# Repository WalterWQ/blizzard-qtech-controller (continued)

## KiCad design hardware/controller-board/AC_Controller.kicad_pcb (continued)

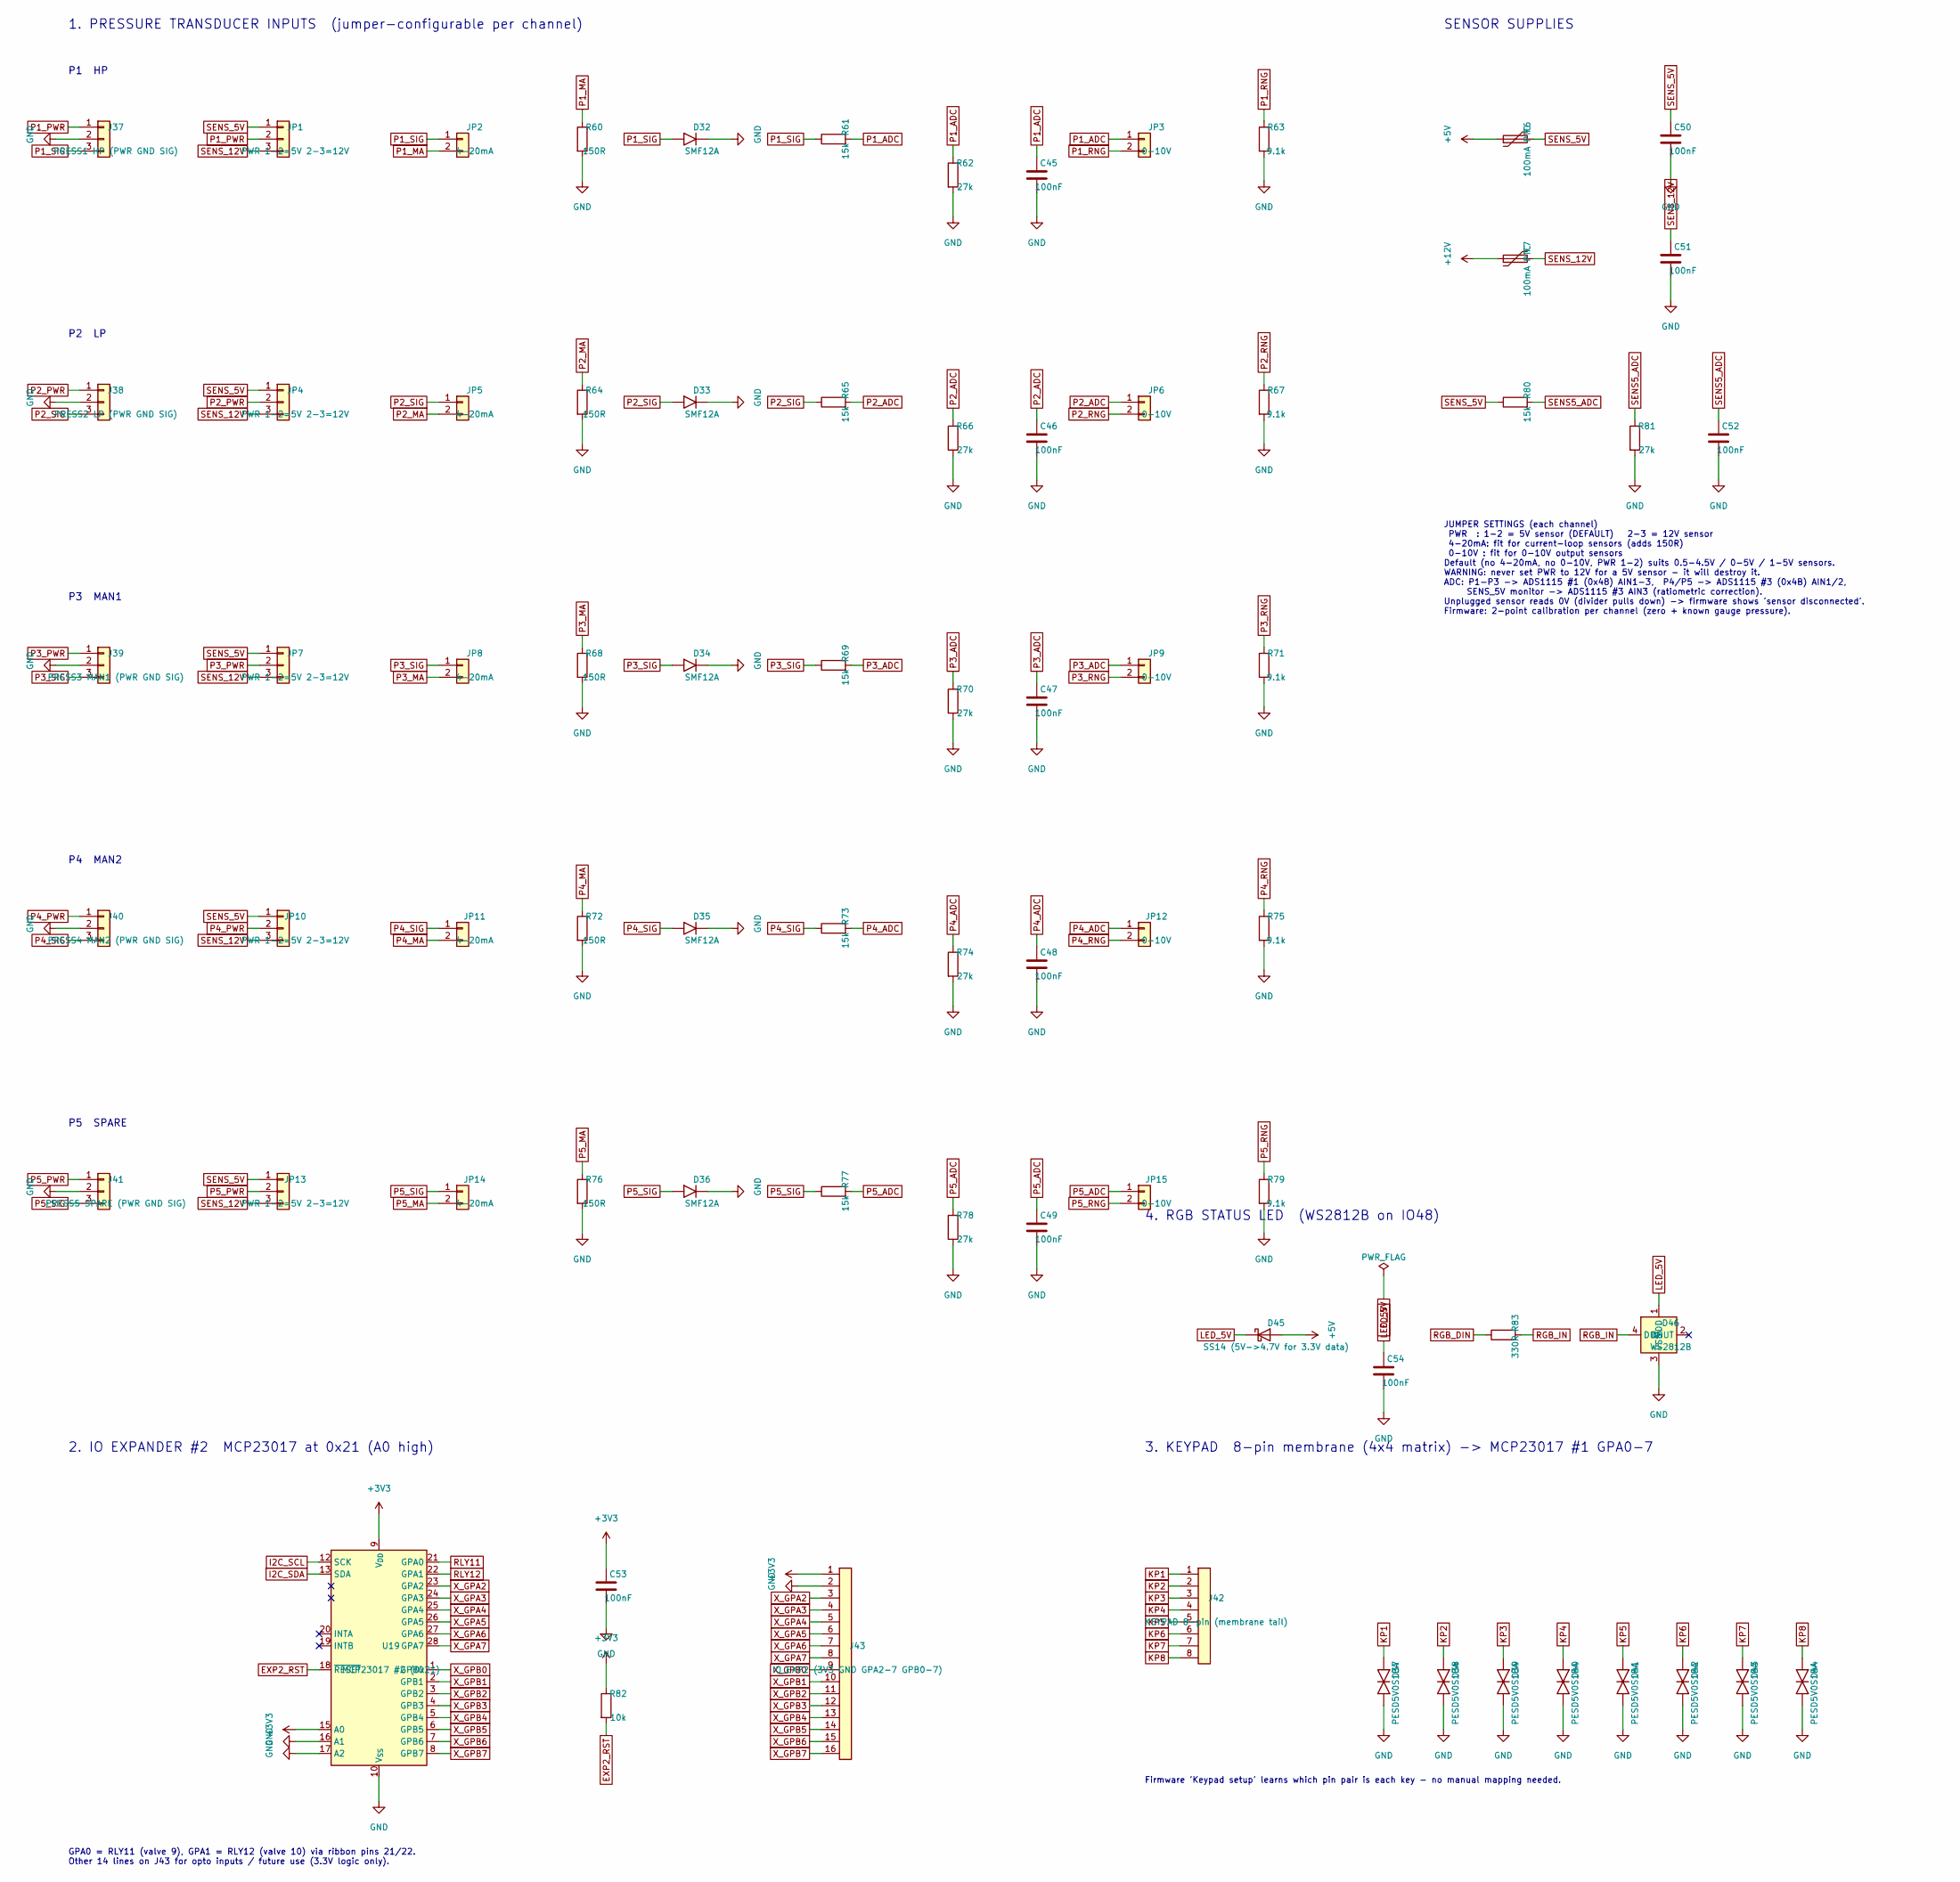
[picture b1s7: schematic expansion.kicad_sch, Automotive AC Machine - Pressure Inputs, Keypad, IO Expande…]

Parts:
C45, C46, C47, C48, C49, C50, C51, C52, C53, C54: 100nF; C_0805_2012Metric
D32, D33, D34, D35, D36: SMF12A; D_SOD-123F
D37, D38, D39, D40, D41, D42, D43, D44: PESD5V0S1BA; D_SOD-323
D45: SS14 (5V->4.7V for 3.3V data); D_SMA
D46: WS2812B; LED_WS2812B_PLCC4_5.0x5.0mm_P3.2mm
F6, F7: 100mA PTC; Fuse_1206_3216Metric
J37: PRESS1 HP (PWR GND SIG); TerminalBlock_Phoenix_MKDS-1,5-3-5.08_1x03_P5.08mm_Horizont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
J38: PRESS2 LP (PWR GND SIG); TerminalBlock_Phoenix_MKDS-1,5-3-5.08_1x03_P5.08mm_Horizont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
J39: PRESS3 MAN1 (PWR GND SIG); TerminalBlock_Phoenix_MKDS-1,5-3-5.08_1x03_P5.08mm_Horizont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
J40: PRESS4 MAN2 (PWR GND SIG); TerminalBlock_Phoenix_MKDS-1,5-3-5.08_1x03_P5.08mm_Horizont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
J41: PRESS5 SPARE (PWR GND SIG); TerminalBlock_Phoenix_MKDS-1,5-3-5.08_1x03_P5.08mm_Horizont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
J42: KEYPAD 8-pin (membrane tail); PinHeader_1x08_P2.54mm_Vertical
J43: IO_EXP2 (3V3 GND GPA2-7 GPB0-7); PinHeader_1x16_P2.54mm_Vertical
JP1, JP4, JP7, JP10, JP13: PWR 1-2=5V 2-3=12V; PinHeader_1x03_P2.54mm_Vertical
JP2, JP5, JP8, JP11, JP14: 4-20mA; PinHeader_1x02_P2.54mm_Vertical
JP3, JP6, JP9, JP12, JP15: 0-10V; PinHeader_1x02_P2.54mm_Vertical
R60, R64, R68, R72, R76: 150R; R_0805_2012Metric
R61, R65, R69, R73, R77, R80: 15k; R_0805_2012Metric
R62, R66, R70, R74, R78, R81: 27k; R_0805_2012Metric
R63, R67, R71, R75, R79: 9.1k; R_0805_2012Metric
R82: 10k; R_0805_2012Metric
R83: 330R; R_0805_2012Metric
U19: MCP23017 #2 (0x21); SOIC-28W_7.5x17.9mm_P1.27mm

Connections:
+3V3: C53.1, J43.1, R82.1, U19.9 (V_{DD}), U19.15 (A0); also elsewhere on the board
+5V: D45.2 (A), F6.1; also elsewhere on the board
+12V: F7.1; also elsewhere on the board
EXP2_RST: R82.2, U19.18 (~RESET)
GND: C45.2, C46.2, C47.2, C48.2, C49.2, C50.2, C51.2, C52.2, C53.2, C54.2, D32.2 (A), D33.2 (A), D34.2 (A), D35.2 (A), D36.2 (A), D37.2 (A2), D38.2 (A2), D39.2 (A2), D40.2 (A2), D41.2 (A2), D42.2 (A2), D43.2 (A2), D44.2 (A2), D46.3 (VSS), J37.2, J38.2, J39.2, J40.2, J41.2, J43.2, R60.2, R62.2, R63.2, R64.2, R66.2, R67.2, R68.2, R70.2, R71.2, R72.2, R74.2, R75.2, R76.2, R78.2, R79.2, R81.2, U19.10 (V_{SS}), U19.16 (A1), U19.17 (A2); also elsewhere on the board
I2C_SCL: U19.12 (SCK); also elsewhere on the board
I2C_SDA: U19.13 (SDA); also elsewhere on the board
KP1: D37.1 (A1), J42.1; also elsewhere on the board
KP2: D38.1 (A1), J42.2; also elsewhere on the board
KP3: D39.1 (A1), J42.3; also elsewhere on the board
KP4: D40.1 (A1), J42.4; also elsewhere on the board
KP5: D41.1 (A1), J42.5; also elsewhere on the board
KP6: D42.1 (A1), J42.6; also elsewhere on the board
KP7: D43.1 (A1), J42.7; also elsewhere on the board
KP8: D44.1 (A1), J42.8; also elsewhere on the board
LED_5V: C54.1, D45.1 (K), D46.1 (VDD)
P1_ADC: C45.1, JP3.1, R61.2, R62.1; also elsewhere on the board
P1_MA: JP2.2, R60.1
P1_PWR: J37.1, JP1.2
P1_RNG: JP3.2, R63.1
P1_SIG: D32.1 (K), J37.3, JP2.1, R61.1
P2_ADC: C46.1, JP6.1, R65.2, R66.1; also elsewhere on the board
P2_MA: JP5.2, R64.1
P2_PWR: J38.1, JP4.2
P2_RNG: JP6.2, R67.1
P2_SIG: D33.1 (K), J38.3, JP5.1, R65.1
P3_ADC: C47.1, JP9.1, R69.2, R70.1; also elsewhere on the board
P3_MA: JP8.2, R68.1
P3_PWR: J39.1, JP7.2
P3_RNG: JP9.2, R71.1
P3_SIG: D34.1 (K), J39.3, JP8.1, R69.1
P4_ADC: C48.1, JP12.1, R73.2, R74.1; also elsewhere on the board
P4_MA: JP11.2, R72.1
P4_PWR: J40.1, JP10.2
P4_RNG: JP12.2, R75.1
P4_SIG: D35.1 (K), J40.3, JP11.1, R73.1
P5_ADC: C49.1, JP15.1, R77.2, R78.1; also elsewhere on the board
P5_MA: JP14.2, R76.1
P5_PWR: J41.1, JP13.2
P5_RNG: JP15.2, R79.1
P5_SIG: D36.1 (K), J41.3, JP14.1, R77.1
RGB_DIN: R83.1; also elsewhere on the board
RGB_IN: D46.4 (DIN), R83.2
RLY11: U19.21 (GPA0); also elsewhere on the board
RLY12: U19.22 (GPA1); also elsewhere on the board
SENS5_ADC: C52.1, R80.2, R81.1; also elsewhere on the board
SENS_5V: C50.1, F6.2, JP1.1, JP4.1, JP7.1, JP10.1, JP13.1, R80.1
SENS_12V: C51.1, F7.2, JP1.3, JP4.3, JP7.3, JP10.3, JP13.3
X_GPA2: J43.3, U19.23 (GPA2)
X_GPA3: J43.4, U19.24 (GPA3)
X_GPA4: J43.5, U19.25 (GPA4)
X_GPA5: J43.6, U19.26 (GPA5)
X_GPA6: J43.7, U19.27 (GPA6)
X_GPA7: J43.8, U19.28 (GPA7)
X_GPB0: J43.9, U19.1 (GPB0)
X_GPB1: J43.10, U19.2 (GPB1)
X_GPB2: J43.11, U19.3 (GPB2)
X_GPB3: J43.12, U19.4 (GPB3)
X_GPB4: J43.13, U19.5 (GPB4)
X_GPB5: J43.14, U19.6 (GPB5)
X_GPB6: J43.15, U19.7 (GPB6)
X_GPB7: J43.16, U19.8 (GPB7)

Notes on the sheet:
1. PRESSURE TRANSDUCER INPUTS (jumper-configurable per channel)
P1 HP
P2 LP
P3 MAN1
P4 MAN2
P5 SPARE
SENSOR SUPPLIES
JUMPER SETTINGS (each channel) PWR : 1-2 = 5V sensor (DEFAULT) 2-3 = 12V sensor 4-20mA: fit for current-loop sensors (adds 150R) 0-10V : fit for 0-10V output sensors Default (no 4-20mA, no 0-10V, PWR 1-2) suits 0.5-4.5V / 0-5V / 1-5V sensors. WARNING: never set PWR to 12V for a 5V sensor - it will 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
2. IO EXPANDER #2 MCP23017 at 0x21 (A0 high)
GPA0 = RLY11 (valve 9), GPA1 = RLY12 (valve 10) via ribbon pins 21/22. Other 14 lines on J43 for opto inputs / future use (3.3V logic only).
3. KEYPAD 8-pin membrane (4x4 matrix) -> MCP23017 #1 GPA0-7
Firmware 'Keypad setup' learns which pin pair is each key - no manual mapping needed.
4. RGB STATUS LED (WS2812B on IO48)

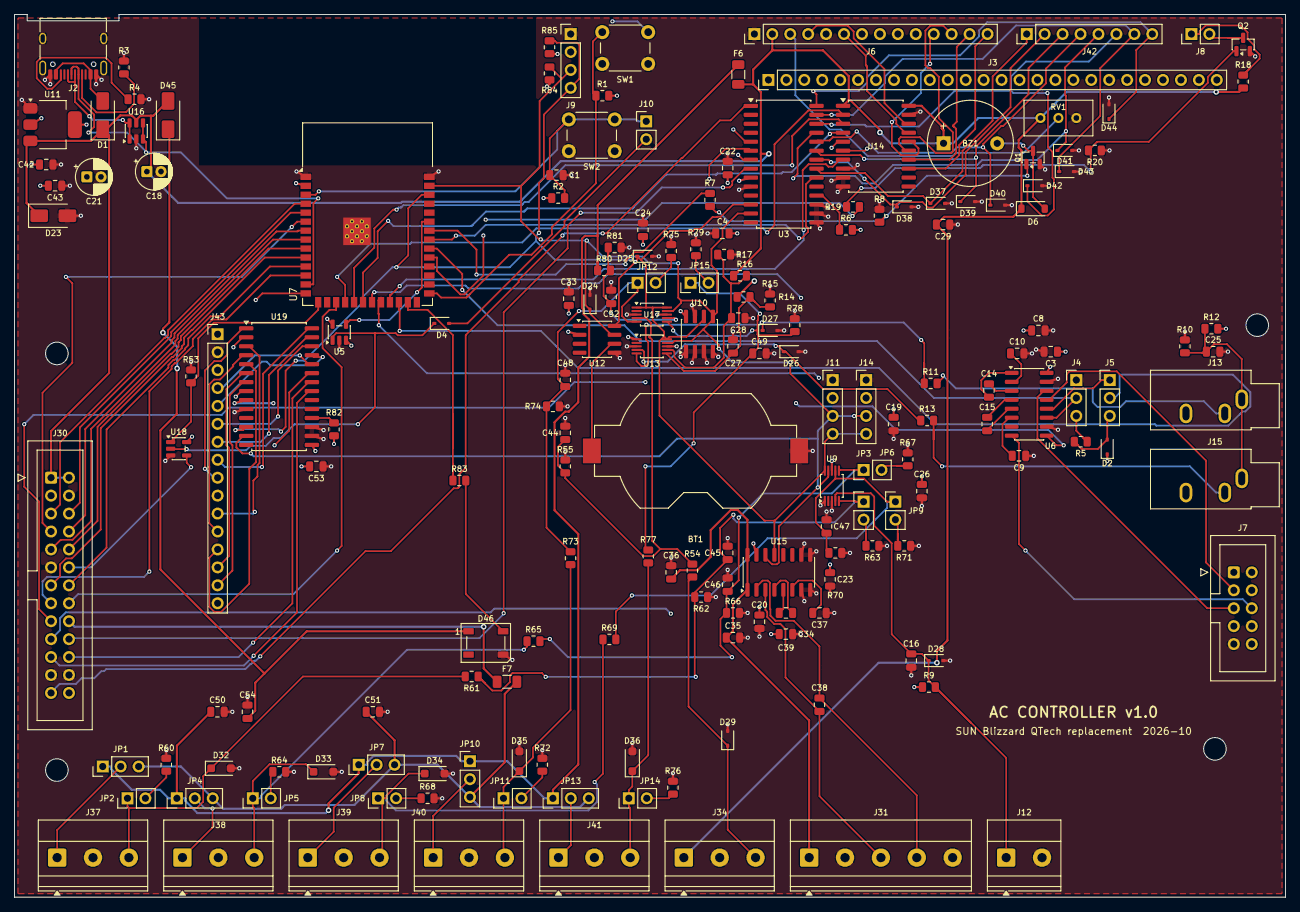
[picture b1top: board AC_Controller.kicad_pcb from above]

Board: 4 copper layers, 180.0 x 125.0 mm, 183 parts (0 on the bottom side), 142 nets.

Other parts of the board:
H1, H2, H3, H4: MountingHole_3.2mm_M3

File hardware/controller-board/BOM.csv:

Line,Qty per board,Part to buy,Package,What it is,References,Notes
1,2,MCP23017-E/SO,SOIC-28 wide,16-bit I/O expander,"U3, U19",
2,1,TPS3823-33DBVR,SOT-23-5,Watchdog / reset chip,U5,
3,1,MAX3232ESE+,SOIC-16,RS-232 transceiver,U6,
4,1,ESP32-S3-WROOM-1-N8 (or -N16R8),Module,Microcontroller module with Wi-Fi,U7,
5,3,ADS1115IDGSR,MSOP-10 (VSSOP),16-bit 4-channel ADC,"U9, U13, U17",
6,1,MB85RC256VPNF,SOIC-8,256kbit FRAM memory,U10,
7,1,AMS1117-3.3,SOT-223,3.3V regulator,U11,
8,1,DS3231MZ+,SOIC-8,Real-time clock,U12,
9,1,SN74HCT245DWR,SOIC-20 wide,8-bit level shifter for LCD,U14,
10,1,NAU7802KGI,SOIC-16,Load-cell ADC,U15,
11,1,USBLC6-2SC6,SOT-23-6,USB ESD protection,U16,
12,1,SN74LVC1G08DBVR,SOT-23-5,Single AND gate,U18,
13,2,AO3400A,SOT-23,N-channel MOSFET,"Q1, Q2",
14,2,SS14,SMA,1A Schottky diode,"D1, D45",
15,2,BAT54WS,SOD-323,Small Schottky diode,"D2, D4",
16,1,1N4148W,SOD-123,Small signal diode,D6,
17,1,SMAJ6.0A,SMA,"TVS diode, 5V rail",D23,
18,14,PESD5V0S1BA,SOD-323,ESD protection diode,"D24, D25, D26, D27, D28, D29, D37, D38, D39, D40, D41, D42, D43, D44",
19,5,SMF12A,SOD-123F,"TVS diode, sensor input","D32, D33, D34, D35, D36",
20,1,WS2812B,5050,RGB status LED,D46,
21,10,10k 1% 0805,0805,Resistor,"R1, R2, R6, R9, R10, R12, R15, R16, R17, R82",
22,2,5.1k 1% 0805,0805,Resistor,"R3, R4",
23,3,1k 1% 0805,0805,Resistor,"R5, R11, R13",
24,2,100R 1% 0805,0805,Resistor,"R7, R19",
25,3,100k 1% 0805,0805,Resistor,"R8, R20, R53",
26,1,47k 1% 0805,0805,Resistor,R14,
27,1,10R 1% 0805,0805,Resistor,R18,
28,7,15k 1% 0805,0805,Resistor,"R54, R61, R65, R69, R73, R77, R80",
29,7,27k 1% 0805,0805,Resistor,"R55, R62, R66, R70, R74, R78, R81",
30,5,150R 1% 0805,0805,Resistor,"R60, R64, R68, R72, R76",
31,5,9.1k 1% 0805,0805,Resistor,"R63, R67, R71, R75, R79",
32,1,330R 1% 0805,0805,Resistor,R83,
33,2,4.7k 1% 0805,0805,Resistor,"R84, R85",
34,1,Bourns 3296W-1-103LF,3296W trimmer,10k trimmer (LCD contrast),RV1,
35,1,1uF 16V X7R 0805,0805,Capacitor,C1,
36,33,100nF X7R 0805,0805,Capacitor,"C3, C4, C8, C9, C10, C14, C15, C16, C19, C20, C22, C23, C26, C27, C28, C29, C33, C36, C37, C38, C42, C43, C44, C45, C46, C47, C48, C49, C50, C51, C52, C53, C54",
37,1,10uF 16V electrolytic,"Radial 5mm, 2mm pitch",Capacitor,C18,
38,1,22uF 16V electrolytic,"Radial 5mm, 2mm pitch",Capacitor,C21,
39,4,10uF 16V X5R 0805,0805,Capacitor,"C24, C25, C34, C35",
40,1,330pF X7R 0805,0805,Capacitor,C39,
41,2,Littelfuse 1206L010 (100mA hold),1206,Resettable fuse,"F6, F7",
42,1,HRO TYPE-C-31-M-12,USB-C,USB-C socket,J2,
43,1,"1x26 pin header, 2.54mm",2.54mm pin header,Pin header,J3,Labels: Front IO; Not connected to anything - decide whether to keep
44,7,"1x3 pin header, 2.54mm",2.54mm pin header,Pin header,"J4, J5, JP1, JP4, JP7, JP10, JP13","Labels: PRINTER_TTL, PRN_SEL, PWR 1-2=5V 2-3=12V; Fit a jumper shunt"
45,1,"1x14 pin header, 2.54mm",2.54mm pin header,Pin header,J6,Labels: LCD
46,1,"2x5 (10-way) box header, 2.54mm",2.54mm box header,Ribbon header,J7,Labels: PRINTER_RS232
47,12,"1x2 pin header, 2.54mm",2.54mm pin header,Pin header,"J8, J10, JP2, JP3, JP5, JP6, JP8, JP9, JP11, JP12, JP14, JP15","Labels: 0-10V, 4-20mA, LCD_BL, WDT_EN; Shunt only if the sensor needs it"
48,3,"1x4 pin header, 2.54mm",2.54mm pin header,Pin header,"J9, J11, J14","Labels: AMBIENT, Conn_01x04, I2C_EXP"
49,1,"Phoenix MKDS 1,5/2-5,08 (1715721) or any 5.08mm 2-way",5.08mm screw terminal,Screw terminal,J12,Labels: TANK_TEMP
50,2,CUI SJ1-3533NG,3.5mm jack,3.5mm jack for current clamp,"J13, J15","Labels: CT_COMP, CT_PUMP"
51,1,"2x13 (26-way) box header, 2.54mm",2.54mm box header,Ribbon header,J30,Labels: Interconnect 2x13 IDC
52,1,"Phoenix MKDS 1,5/5-5,08 (1715750) or any 5.08mm 5-way",5.08mm screw terminal,Screw terminal,J31,Labels: LOAD_CELL (E+ E- S+ S- SHLD)
53,6,"Phoenix MKDS 1,5/3-5,08 (1715734) or any 5.08mm 3-way",5.08mm screw terminal,Screw terminal,"J34, J37, J38, J39, J40, J41","Labels: LEAK_SENSOR (+5V GND SIG), PRESS1 HP (PWR GND SIG), PRESS2 LP (PWR GND SIG), PRESS3 MAN1 (PWR GND SIG), PRESS4 MAN2 (PWR GND SIG), PRESS5 SPARE (PWR GND SIG)"
54,1,"1x8 pin header, 2.54mm",2.54mm pin header,Pin header,J42,Labels: KEYPAD 8-pin (membrane tail)
55,1,"1x16 pin header, 2.54mm",2.54mm pin header,Pin header,J43,Labels: IO_EXP2 (3V3 GND GPA2-7 GPB0-7)
56,2,6x6mm tactile switch,6mm tactile,Push button,"SW1, SW2",
57,1,"5V magnetic buzzer, 12mm","12mm buzzer, 7.6mm pitch",Buzzer,BZ1,
58,1,Keystone 1058,CR2032 holder,CR2032 holder,BT1,
Total,,Total parts placed per board / parts to buy,,,,

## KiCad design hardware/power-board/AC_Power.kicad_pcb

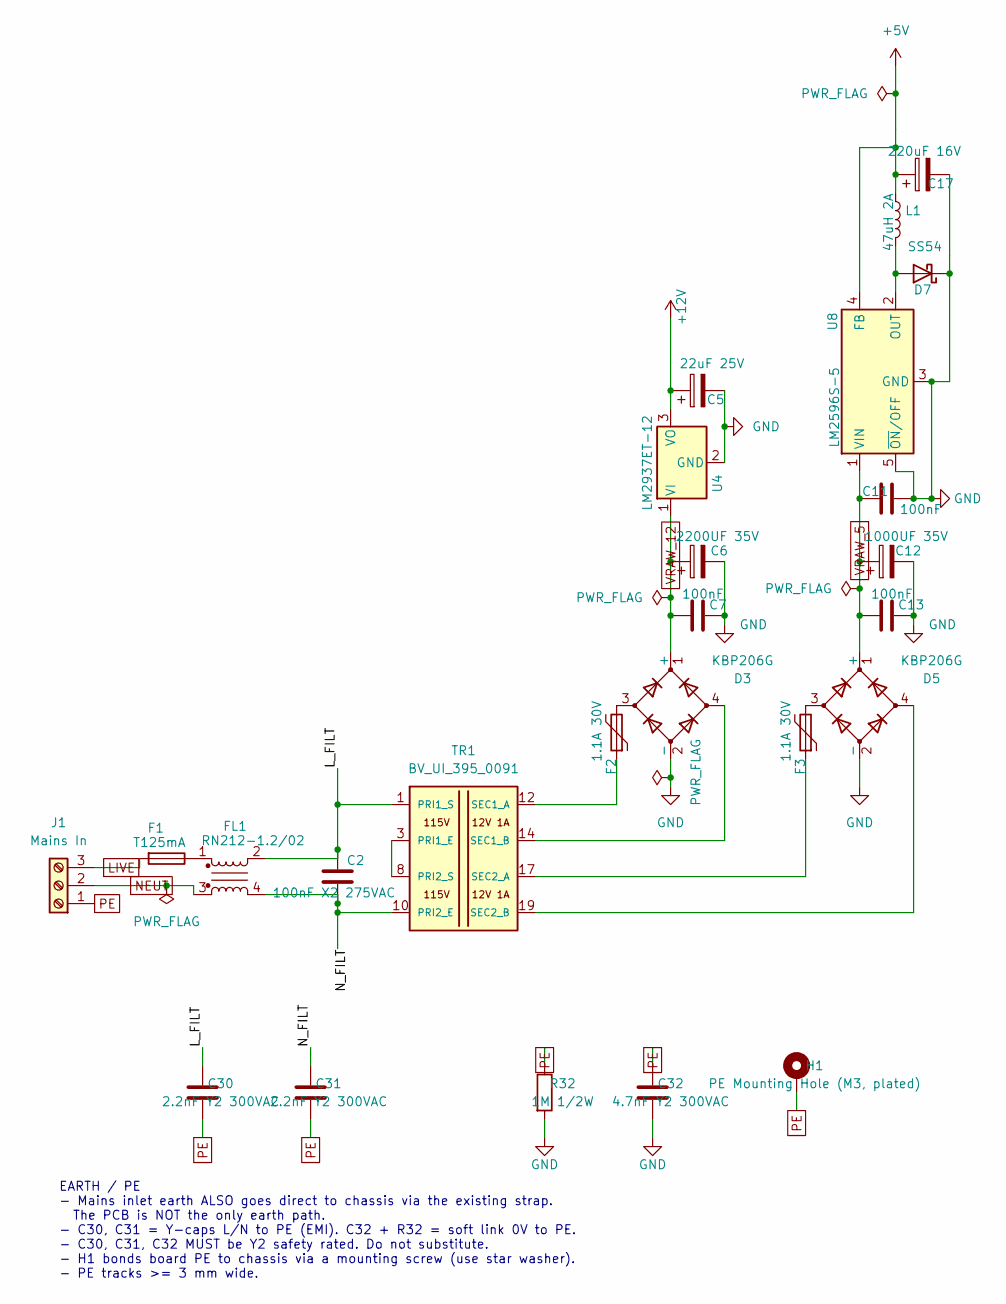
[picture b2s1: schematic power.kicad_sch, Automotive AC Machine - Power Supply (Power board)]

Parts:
C2: 100nF X2 275VAC; C_Rect_L13.0mm_W6.0mm_P10.00mm_FKS3_FKP3_MKS4
C5: 22uF 25V; CP_Radial_D5.0mm_P2.00mm
C6: 2200UF 35V; CP_Radial_D16.0mm_P7.50mm
C7, C11, C13: 100nF; C_0805_2012Metric
C12: 1000UF 35V; CP_Radial_D12.5mm_P5.00mm
C17: 220uF 16V; CP_Radial_D8.0mm_P3.50mm
C30, C31: 2.2nF Y2 300VAC; C_Disc_D7.5mm_W5.0mm_P10.00mm
C32: 4.7nF Y2 300VAC; C_Disc_D7.5mm_W5.0mm_P10.00mm
D3, D5: KBP206G; KBP_P-AC-AC-M
D7: SS54; D_SMC
F1: T125mA; Fuseholder_Cylinder-5x20mm_Schurter_FAB_0031-355x_Horizonta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
F2, F3: 1.1A 30V; Fuse_1812_4532Metric
FL1: RN212-1.2/02; Choke_Schaffner_RN212-04-12.5x18.0mm
H1: PE Mounting Hole (M3, plated); MountingHole_3.2mm_M3_Pad_Via
J1: Mains In; KF7.62_3P
L1: 47uH 2A; L_12x12mm_H8mm
R32: 1M 1/2W; R_Axial_DIN0414_L11.9mm_D4.5mm_P15.24mm_Horizontal
TR1: BV_UI_395_0091; Hahn_UI39_BV_UI_395
U4: LM2937ET-12; TO-220-3_Vertical
U8: LM2596S-5; TO-263-5_TabPin3

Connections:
+5V: C17.1, L1.1, U8.4 (FB); also elsewhere on the board
+12V: C5.1, U4.3 (VO); also elsewhere on the board
GND: C5.2, C6.2, C7.1, C11.1, C12.2, C13.1, C17.2, C32.2, D3.2 (-), D5.2 (-), D7.1 (K), R32.2, U4.2 (GND), U8.3 (GND), U8.5 (~ON/OFF); also elsewhere on the board
LIVE: F1.2, J1.3; also elsewhere on the board
L_FILT: C2.2, C30.1, FL1.2, TR1.1 (PRI1_S)
NEUT: FL1.3, J1.2; also elsewhere on the board
N_D3.3: D3.3, F2.2
N_D3.4: D3.4, TR1.14 (SEC1_B)
N_D5.3: D5.3, F3.2
N_D5.4: D5.4, TR1.19 (SEC2_B)
N_D7.2: D7.2 (A), L1.2, U8.2 (OUT)
N_F1.1: F1.1, FL1.1
N_F2.1: F2.1, TR1.12 (SEC1_A)
N_F3.1: F3.1, TR1.17 (SEC2_A)
N_FILT: C2.1, C31.1, FL1.4, TR1.10 (PRI2_E)
N_TR1.3: TR1.3 (PRI1_E), TR1.8 (PRI2_S)
PE: C30.2, C31.2, C32.1, H1.1, J1.1, R32.1; also elsewhere on the board
VRAW_5: C11.2, C12.1, C13.2, D5.1 (+), U8.1 (VIN)
VRAW_12: C6.1, C7.2, D3.1 (+), U4.1 (VI)

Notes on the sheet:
EARTH / PE - Mains inlet earth ALSO goes direct to chassis via the existing strap. The PCB is NOT the only earth path. - C30, C31 = Y-caps L/N to PE (EMI). C32 + R32 = soft link 0V to PE. - C30, C31, C32 MUST be Y2 safety rated. Do not substitute. - H1 bonds board PE to chassis via a mounting screw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

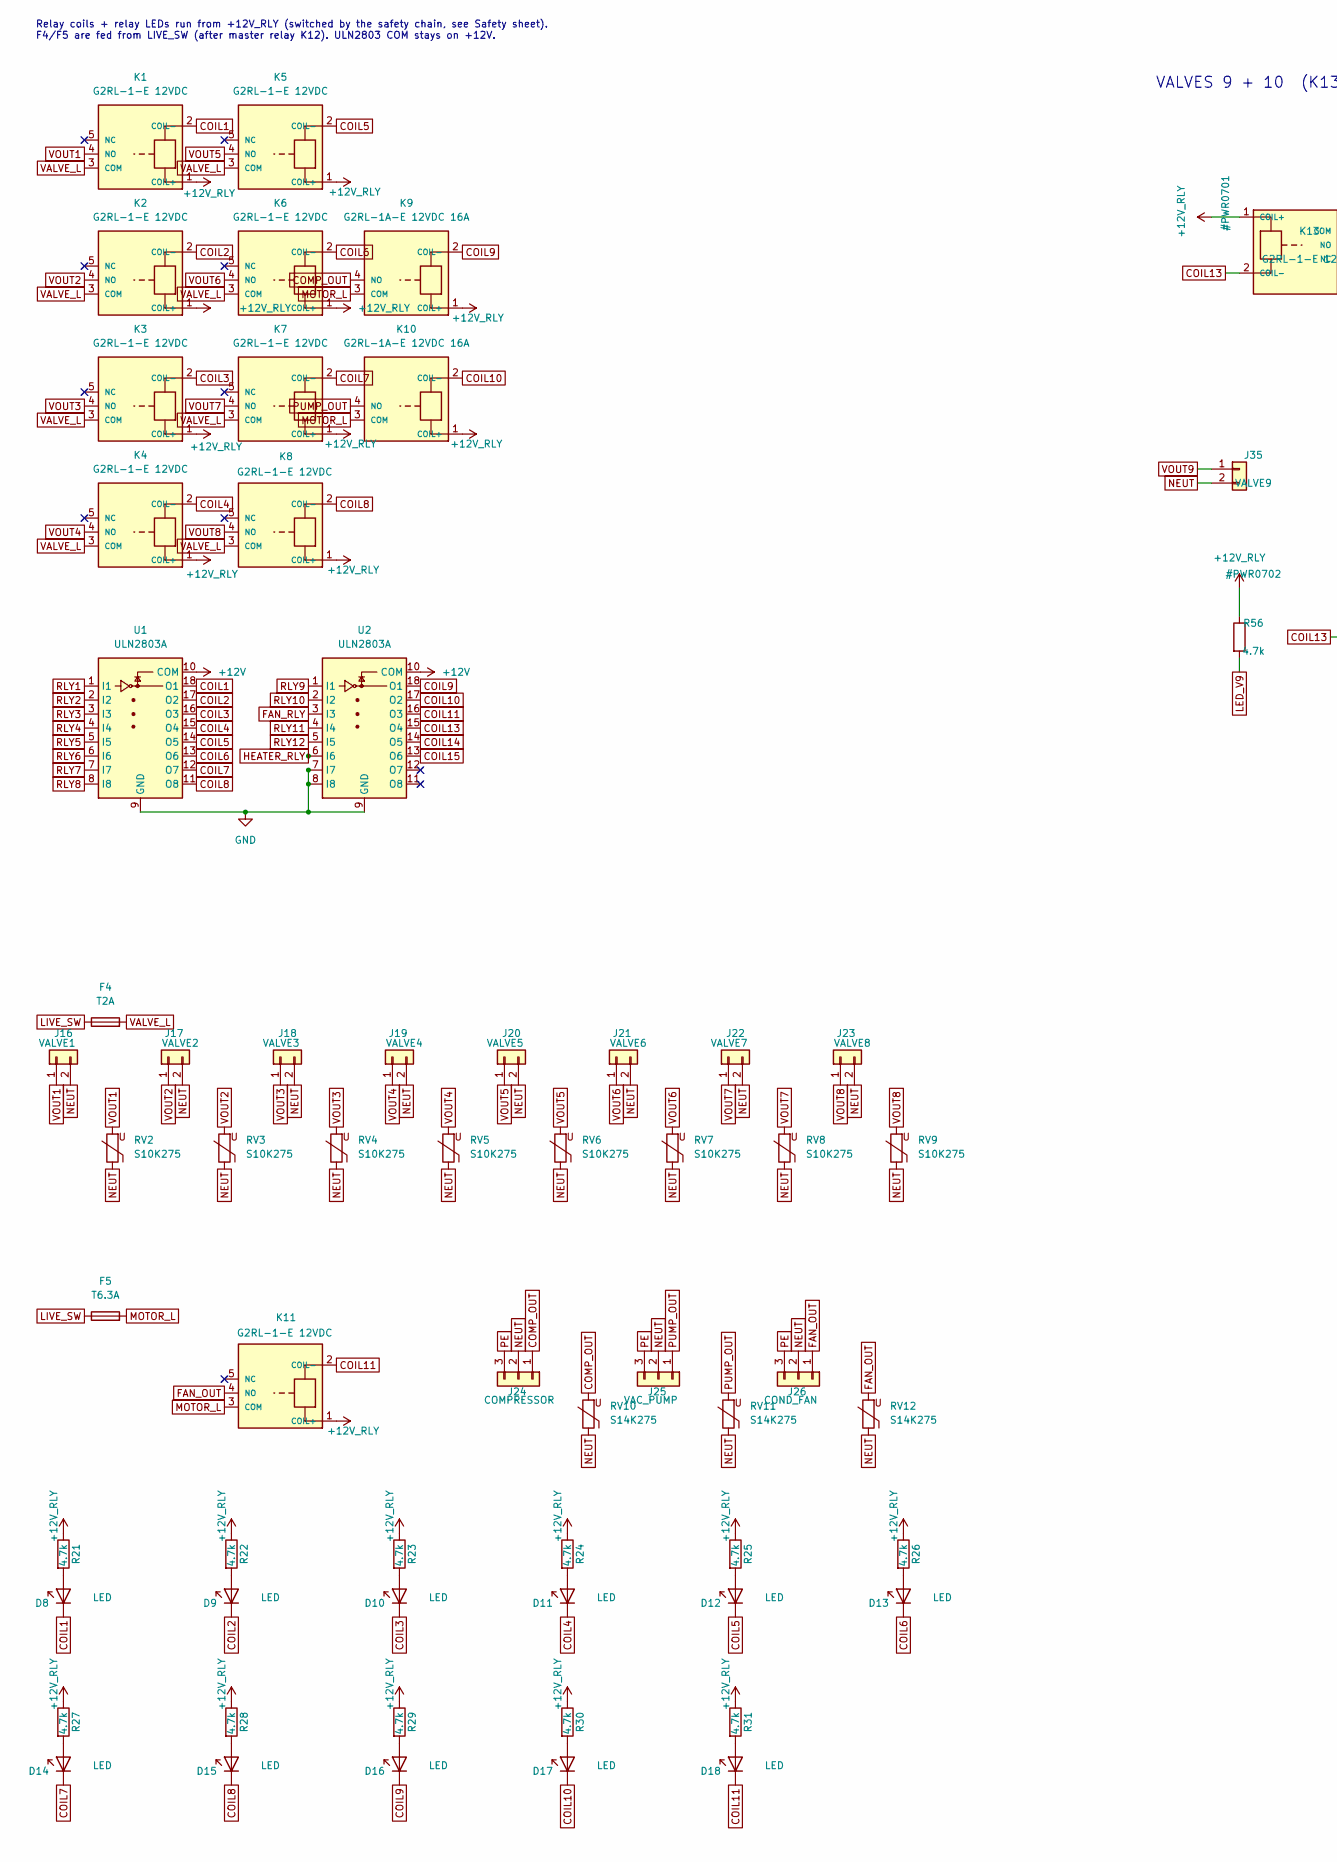
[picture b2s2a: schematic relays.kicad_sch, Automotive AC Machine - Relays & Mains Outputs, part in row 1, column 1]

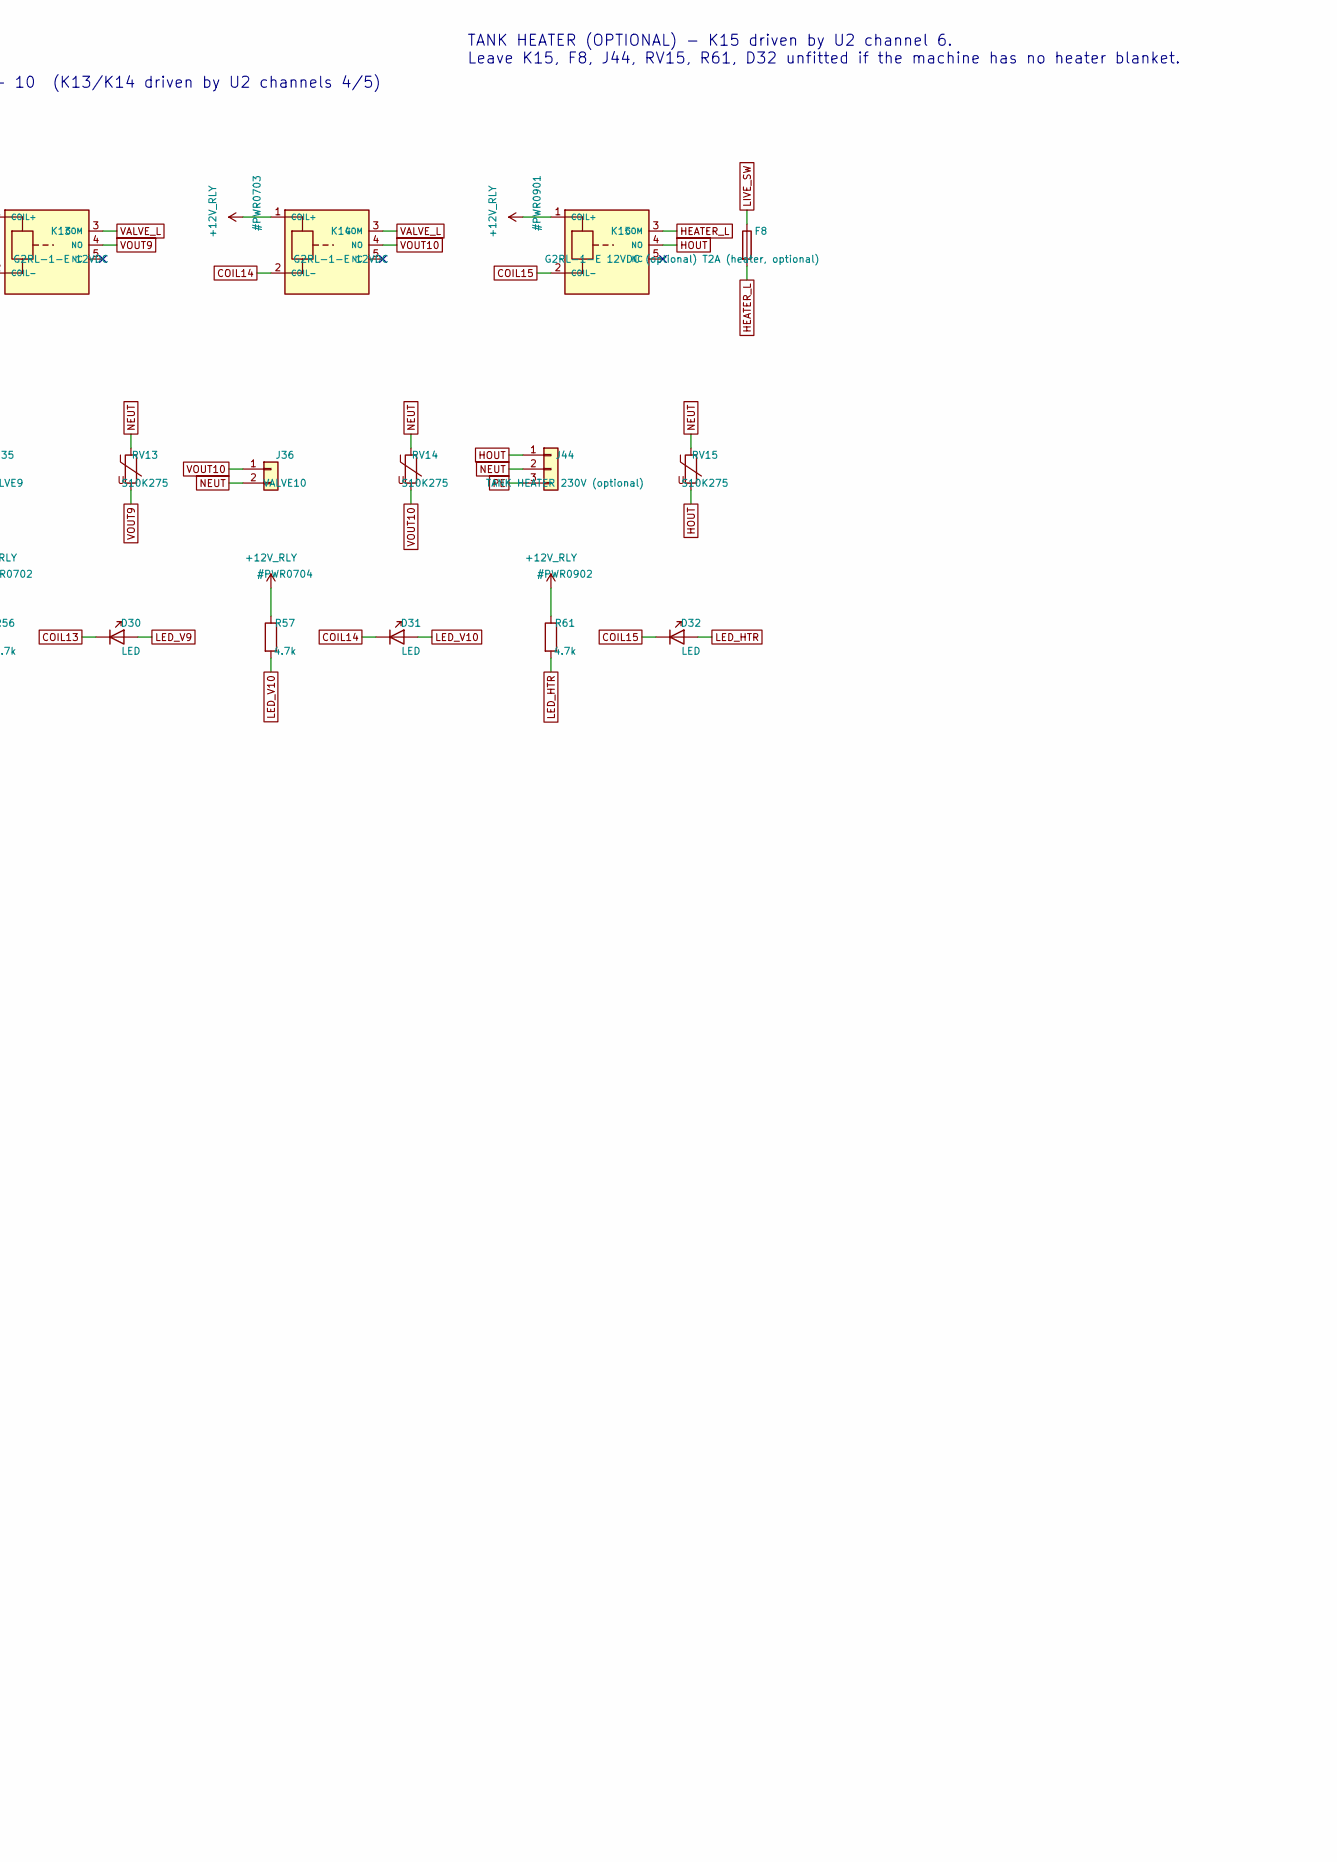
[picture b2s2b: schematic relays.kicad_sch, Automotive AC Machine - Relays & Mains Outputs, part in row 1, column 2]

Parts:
D8, D9, D10, D11, D12, D13, D14, D15, D16, D17, D18, D30, D31, D32: LED; LED_0805_2012Metric
F4: T2A; Fuseholder_Cylinder-5x20mm_Schurter_FAB_0031-355x_Horizonta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
F5: T6.3A; Fuseholder_Cylinder-5x20mm_Schurter_FAB_0031-355x_Horizonta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
F8: T2A (heater, optional); Fuseholder_Cylinder-5x20mm_Schurter_FAB_0031-355x_Horizonta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
J16: VALVE1; KF7.62_2P
J17: VALVE2; KF7.62_2P
J18: VALVE3; KF7.62_2P
J19: VALVE4; KF7.62_2P
J20: VALVE5; KF7.62_2P
J21: VALVE6; KF7.62_2P
J22: VALVE7; KF7.62_2P
J23: VALVE8; KF7.62_2P
J24: COMPRESSOR; KF7.62_3P
J25: VAC_PUMP; KF7.62_3P
J26: COND_FAN; KF7.62_3P
J35: VALVE9; KF7.62_2P
J36: VALVE10; KF7.62_2P
J44: TANK HEATER 230V (optional); KF7.62_3P
K1, K2, K3, K4, K5, K6, K7, K8, K11, K13, K14: G2RL-1-E 12VDC; Relay_G2RL-1-E_QT
K9, K10: G2RL-1A-E 12VDC 16A; Relay_G2RL-1A-E_QT
K15: G2RL-1-E 12VDC (optional); Relay_G2RL-1-E_QT
R21, R22, R23, R24, R25, R26, R27, R28, R29, R30, R31, R56, R57, R61: 4.7k; R_0805_2012Metric
RV2, RV3, RV4, RV5, RV6, RV7, RV8, RV9, RV13, RV14, RV15: S10K275; RV_Disc_D12mm_W5.4mm_P7.5mm
RV10, RV11, RV12: S14K275; RV_Disc_D15.5mm_W5.4mm_P7.5mm
U1, U2: ULN2803A; DIP-18_W7.62mm_Socket

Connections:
+12V: U1.10 (COM), U2.10 (COM); also elsewhere on the board
+12V_RLY: K1.1 (COIL+), K2.1 (COIL+), K3.1 (COIL+), K4.1 (COIL+), K5.1 (COIL+), K6.1 (COIL+), K7.1 (COIL+), K8.1 (COIL+), K9.1 (COIL+), K10.1 (COIL+), K11.1 (COIL+), K13.1 (COIL+), K14.1 (COIL+), K15.1 (COIL+), R21.1, R22.1, R23.1, R24.1, R25.1, R26.1, R27.1, R28.1, R29.1, R30.1, R31.1, R56.1, R57.1, R61.1; also elsewhere on the board
COIL1: D8.1 (K), K1.2 (COIL-), U1.18 (O1)
COIL2: D9.1 (K), K2.2 (COIL-), U1.17 (O2)
COIL3: D10.1 (K), K3.2 (COIL-), U1.16 (O3)
COIL4: D11.1 (K), K4.2 (COIL-), U1.15 (O4)
COIL5: D12.1 (K), K5.2 (COIL-), U1.14 (O5)
COIL6: D13.1 (K), K6.2 (COIL-), U1.13 (O6)
COIL7: D14.1 (K), K7.2 (COIL-), U1.12 (O7)
COIL8: D15.1 (K), K8.2 (COIL-), U1.11 (O8)
COIL9: D16.1 (K), K9.2 (COIL-), U2.18 (O1)
COIL10: D17.1 (K), K10.2 (COIL-), U2.17 (O2)
COIL11: D18.1 (K), K11.2 (COIL-), U2.16 (O3)
COIL13: D30.1 (K), K13.2 (COIL-), U2.15 (O4)
COIL14: D31.1 (K), K14.2 (COIL-), U2.14 (O5)
COIL15: D32.1 (K), K15.2 (COIL-), U2.13 (O6)
COMP_OUT: J24.1, K9.4 (NO), RV10.2
FAN_OUT: J26.1, K11.4 (NO), RV12.2
FAN_RLY: U2.3 (I3); also elsewhere on the board
GND: U1.9 (GND), U2.7 (I7), U2.8 (I8), U2.9 (GND); also elsewhere on the board
HEATER_L: F8.2, K15.3 (COM)
HEATER_RLY: U2.6 (I6); also elsewhere on the board
HOUT: J44.1, K15.4 (NO), RV15.2
LED_HTR: D32.2 (A), R61.2
LED_V9: D30.2 (A), R56.2
LED_V10: D31.2 (A), R57.2
LIVE_SW: F4.1, F5.1, F8.1; also elsewhere on the board
MOTOR_L: F5.2, K9.3 (COM), K10.3 (COM), K11.3 (COM)
NEUT: J16.2, J17.2, J18.2, J19.2, J20.2, J21.2, J22.2, J23.2, J24.2, J25.2, J26.2, J35.2, J36.2, J44.2, RV2.1, RV3.1, RV4.1, RV5.1, RV6.1, RV7.1, RV8.1, RV9.1, RV10.1, RV11.1, RV12.1, RV13.1, RV14.1, RV15.1; also elsewhere on the board
N_D8.2: D8.2 (A), R21.2
N_D9.2: D9.2 (A), R22.2
N_D10.2: D10.2 (A), R23.2
N_D11.2: D11.2 (A), R24.2
N_D12.2: D12.2 (A), R25.2
N_D13.2: D13.2 (A), R26.2
N_D14.2: D14.2 (A), R27.2
N_D15.2: D15.2 (A), R28.2
N_D16.2: D16.2 (A), R29.2
N_D17.2: D17.2 (A), R30.2
N_D18.2: D18.2 (A), R31.2
N_K1.5: K1.5 (NC)
N_K2.5: K2.5 (NC)
N_K3.5: K3.5 (NC)
N_K4.5: K4.5 (NC)
N_K5.5: K5.5 (NC)
N_K6.5: K6.5 (NC)
N_K7.5: K7.5 (NC)
N_K8.5: K8.5 (NC)
N_K11.5: K11.5 (NC)
N_K13.5: K13.5 (NC)
N_K14.5: K14.5 (NC)
N_K15.5: K15.5 (NC)
N_U2.11: U2.11 (O8)
N_U2.12: U2.12 (O7)
PE: J24.3, J25.3, J26.3, J44.3; also elsewhere on the board
PUMP_OUT: J25.1, K10.4 (NO), RV11.2
RLY1: U1.1 (I1); also elsewhere on the board
RLY2: U1.2 (I2); also elsewhere on the board
RLY3: U1.3 (I3); also elsewhere on the board
RLY4: U1.4 (I4); also elsewhere on the board
RLY5: U1.5 (I5); also elsewhere on the board
RLY6: U1.6 (I6); also elsewhere on the board
RLY7: U1.7 (I7); also elsewhere on the board
RLY8: U1.8 (I8); also elsewhere on the board
RLY9: U2.1 (I1); also elsewhere on the board
RLY10: U2.2 (I2); also elsewhere on the board
RLY11: U2.4 (I4); also elsewhere on the board
RLY12: U2.5 (I5); also elsewhere on the board
VALVE_L: F4.2, K1.3 (COM), K2.3 (COM), K3.3 (COM), K4.3 (COM), K5.3 (COM), K6.3 (COM), K7.3 (COM), K8.3 (COM), K13.3 (COM), K14.3 (COM)
VOUT1: J16.1, K1.4 (NO), RV2.2
VOUT2: J17.1, K2.4 (NO), RV3.2
VOUT3: J18.1, K3.4 (NO), RV4.2
VOUT4: J19.1, K4.4 (NO), RV5.2
VOUT5: J20.1, K5.4 (NO), RV6.2
VOUT6: J21.1, K6.4 (NO), RV7.2
VOUT7: J22.1, K7.4 (NO), RV8.2
VOUT8: J23.1, K8.4 (NO), RV9.2
VOUT9: J35.1, K13.4 (NO), RV13.2
VOUT10: J36.1, K14.4 (NO), RV14.2

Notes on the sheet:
Relay coils + relay LEDs run from +12V_RLY (switched by the safety chain, see Safety sheet). F4/F5 are fed from LIVE_SW (after master relay K12). ULN2803 COM stays on +12V.
VALVES 9 + 10 (K13/K14 driven by U2 channels 4/5)
TANK HEATER (OPTIONAL) - K15 driven by U2 channel 6. Leave K15, F8, J44, RV15, R61, D32 unfitted if the machine has no heater blanket.
